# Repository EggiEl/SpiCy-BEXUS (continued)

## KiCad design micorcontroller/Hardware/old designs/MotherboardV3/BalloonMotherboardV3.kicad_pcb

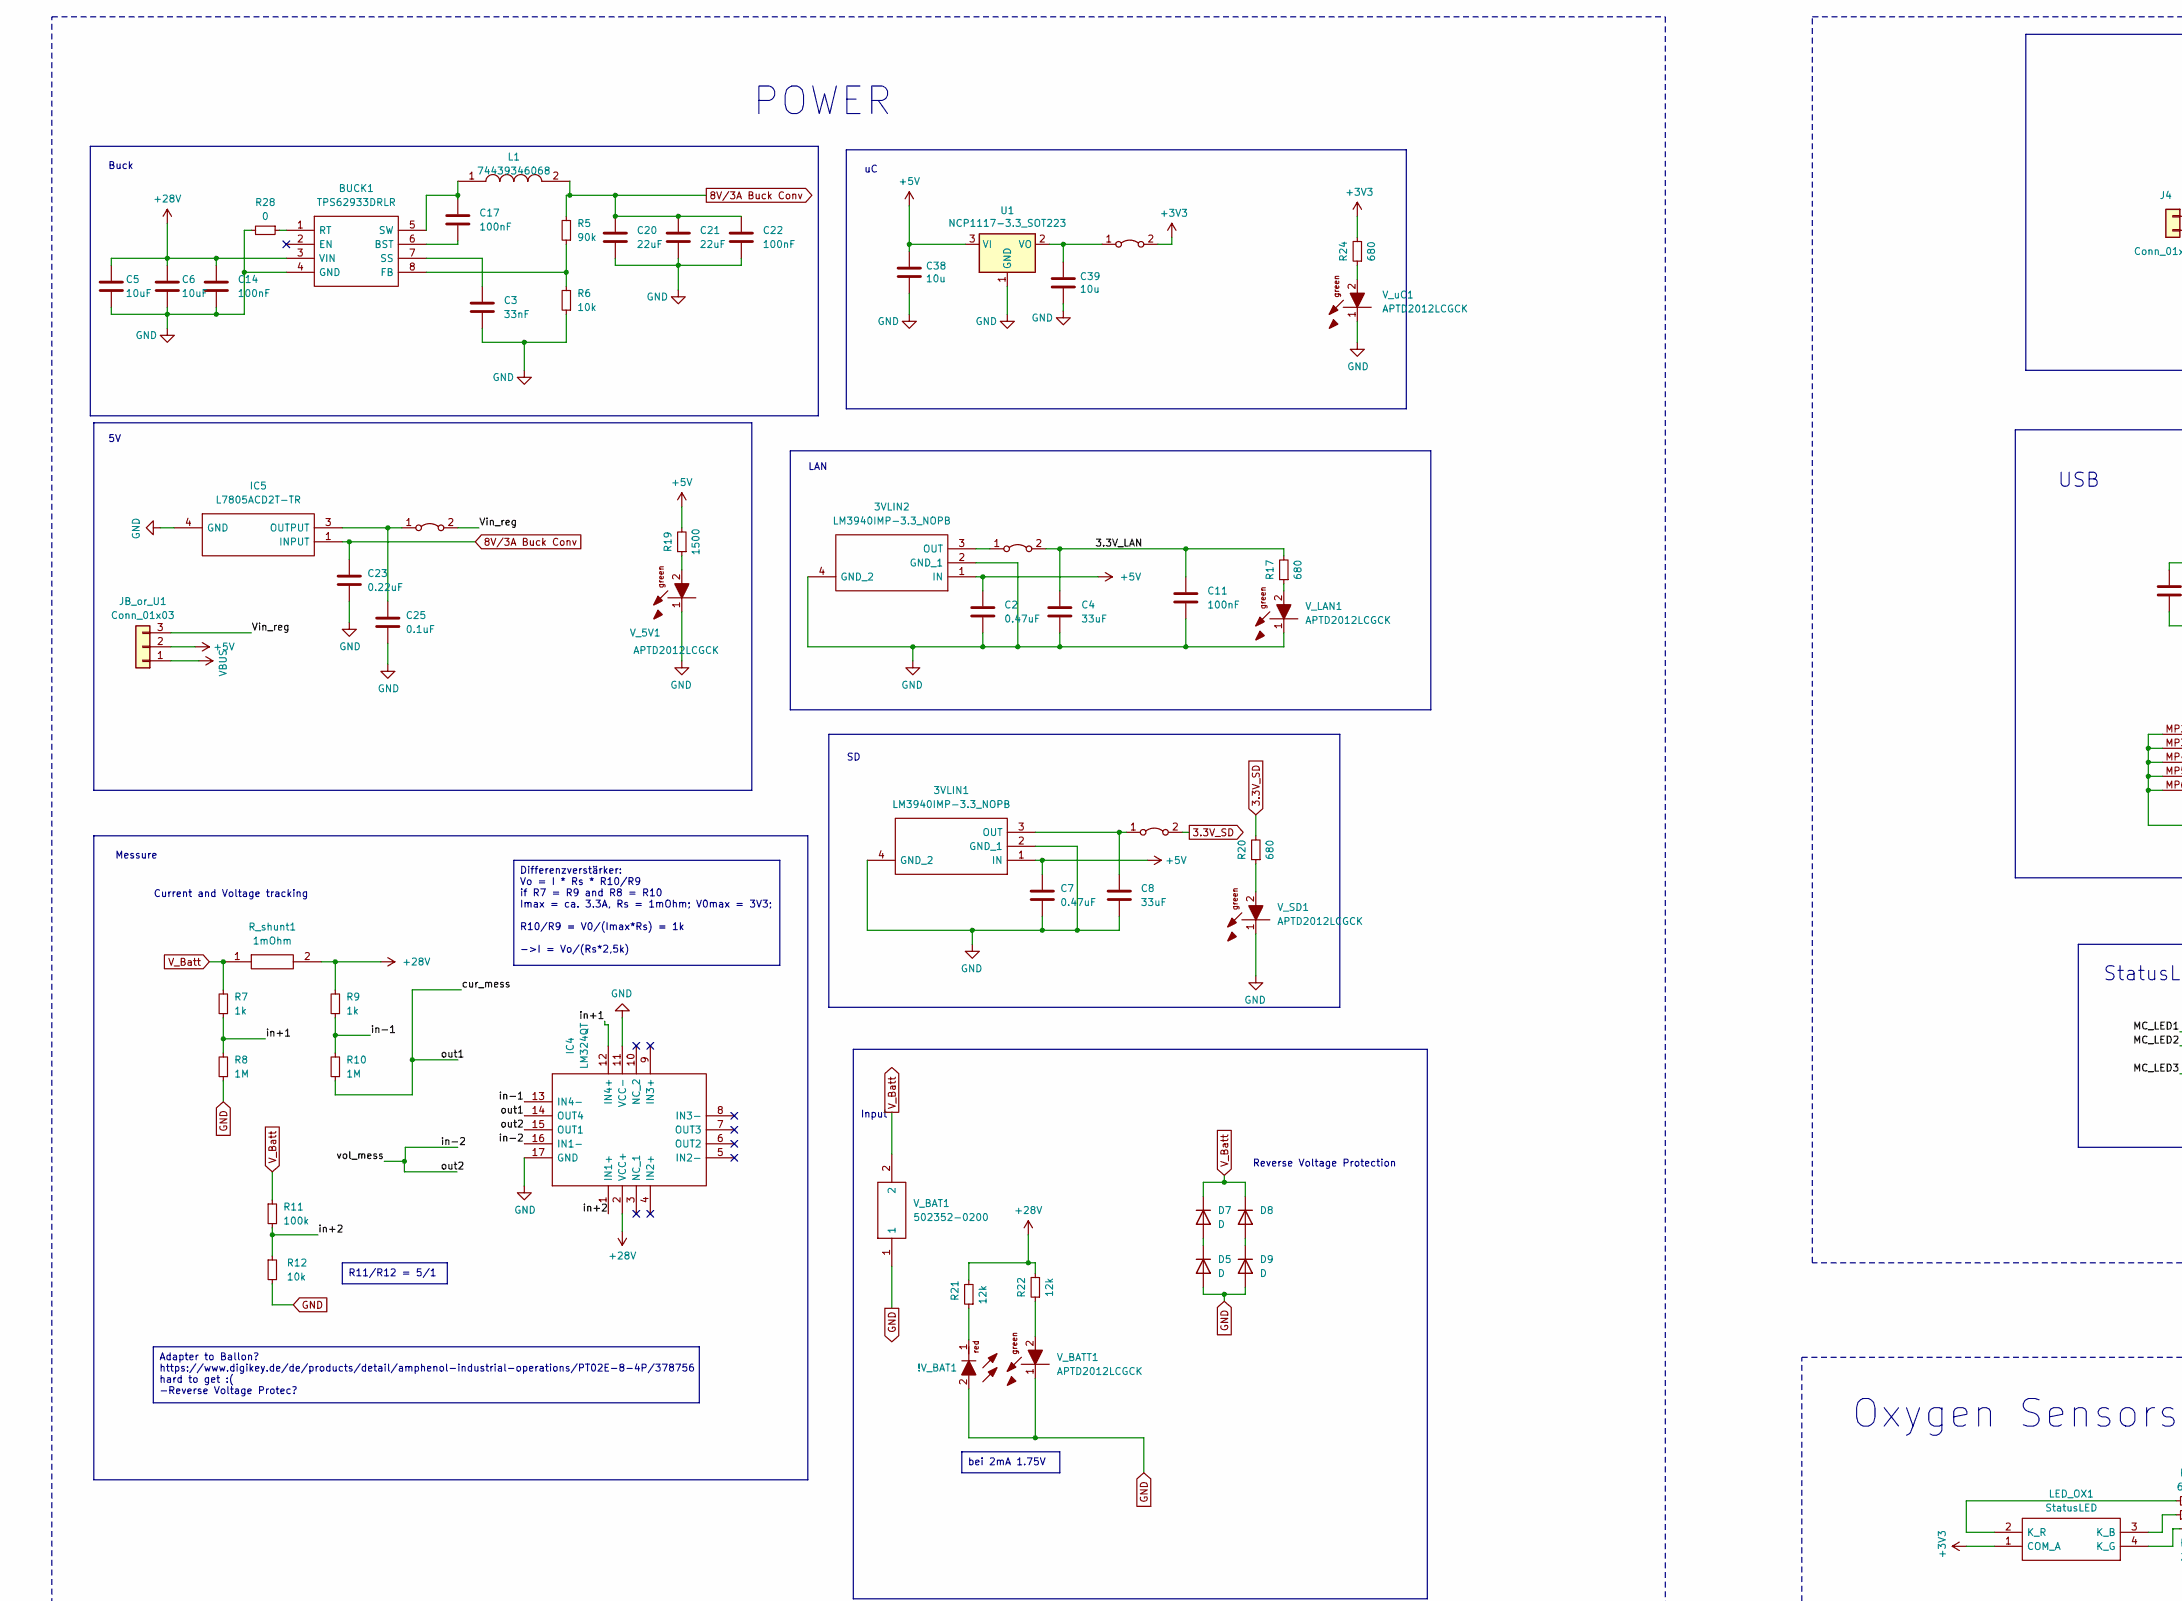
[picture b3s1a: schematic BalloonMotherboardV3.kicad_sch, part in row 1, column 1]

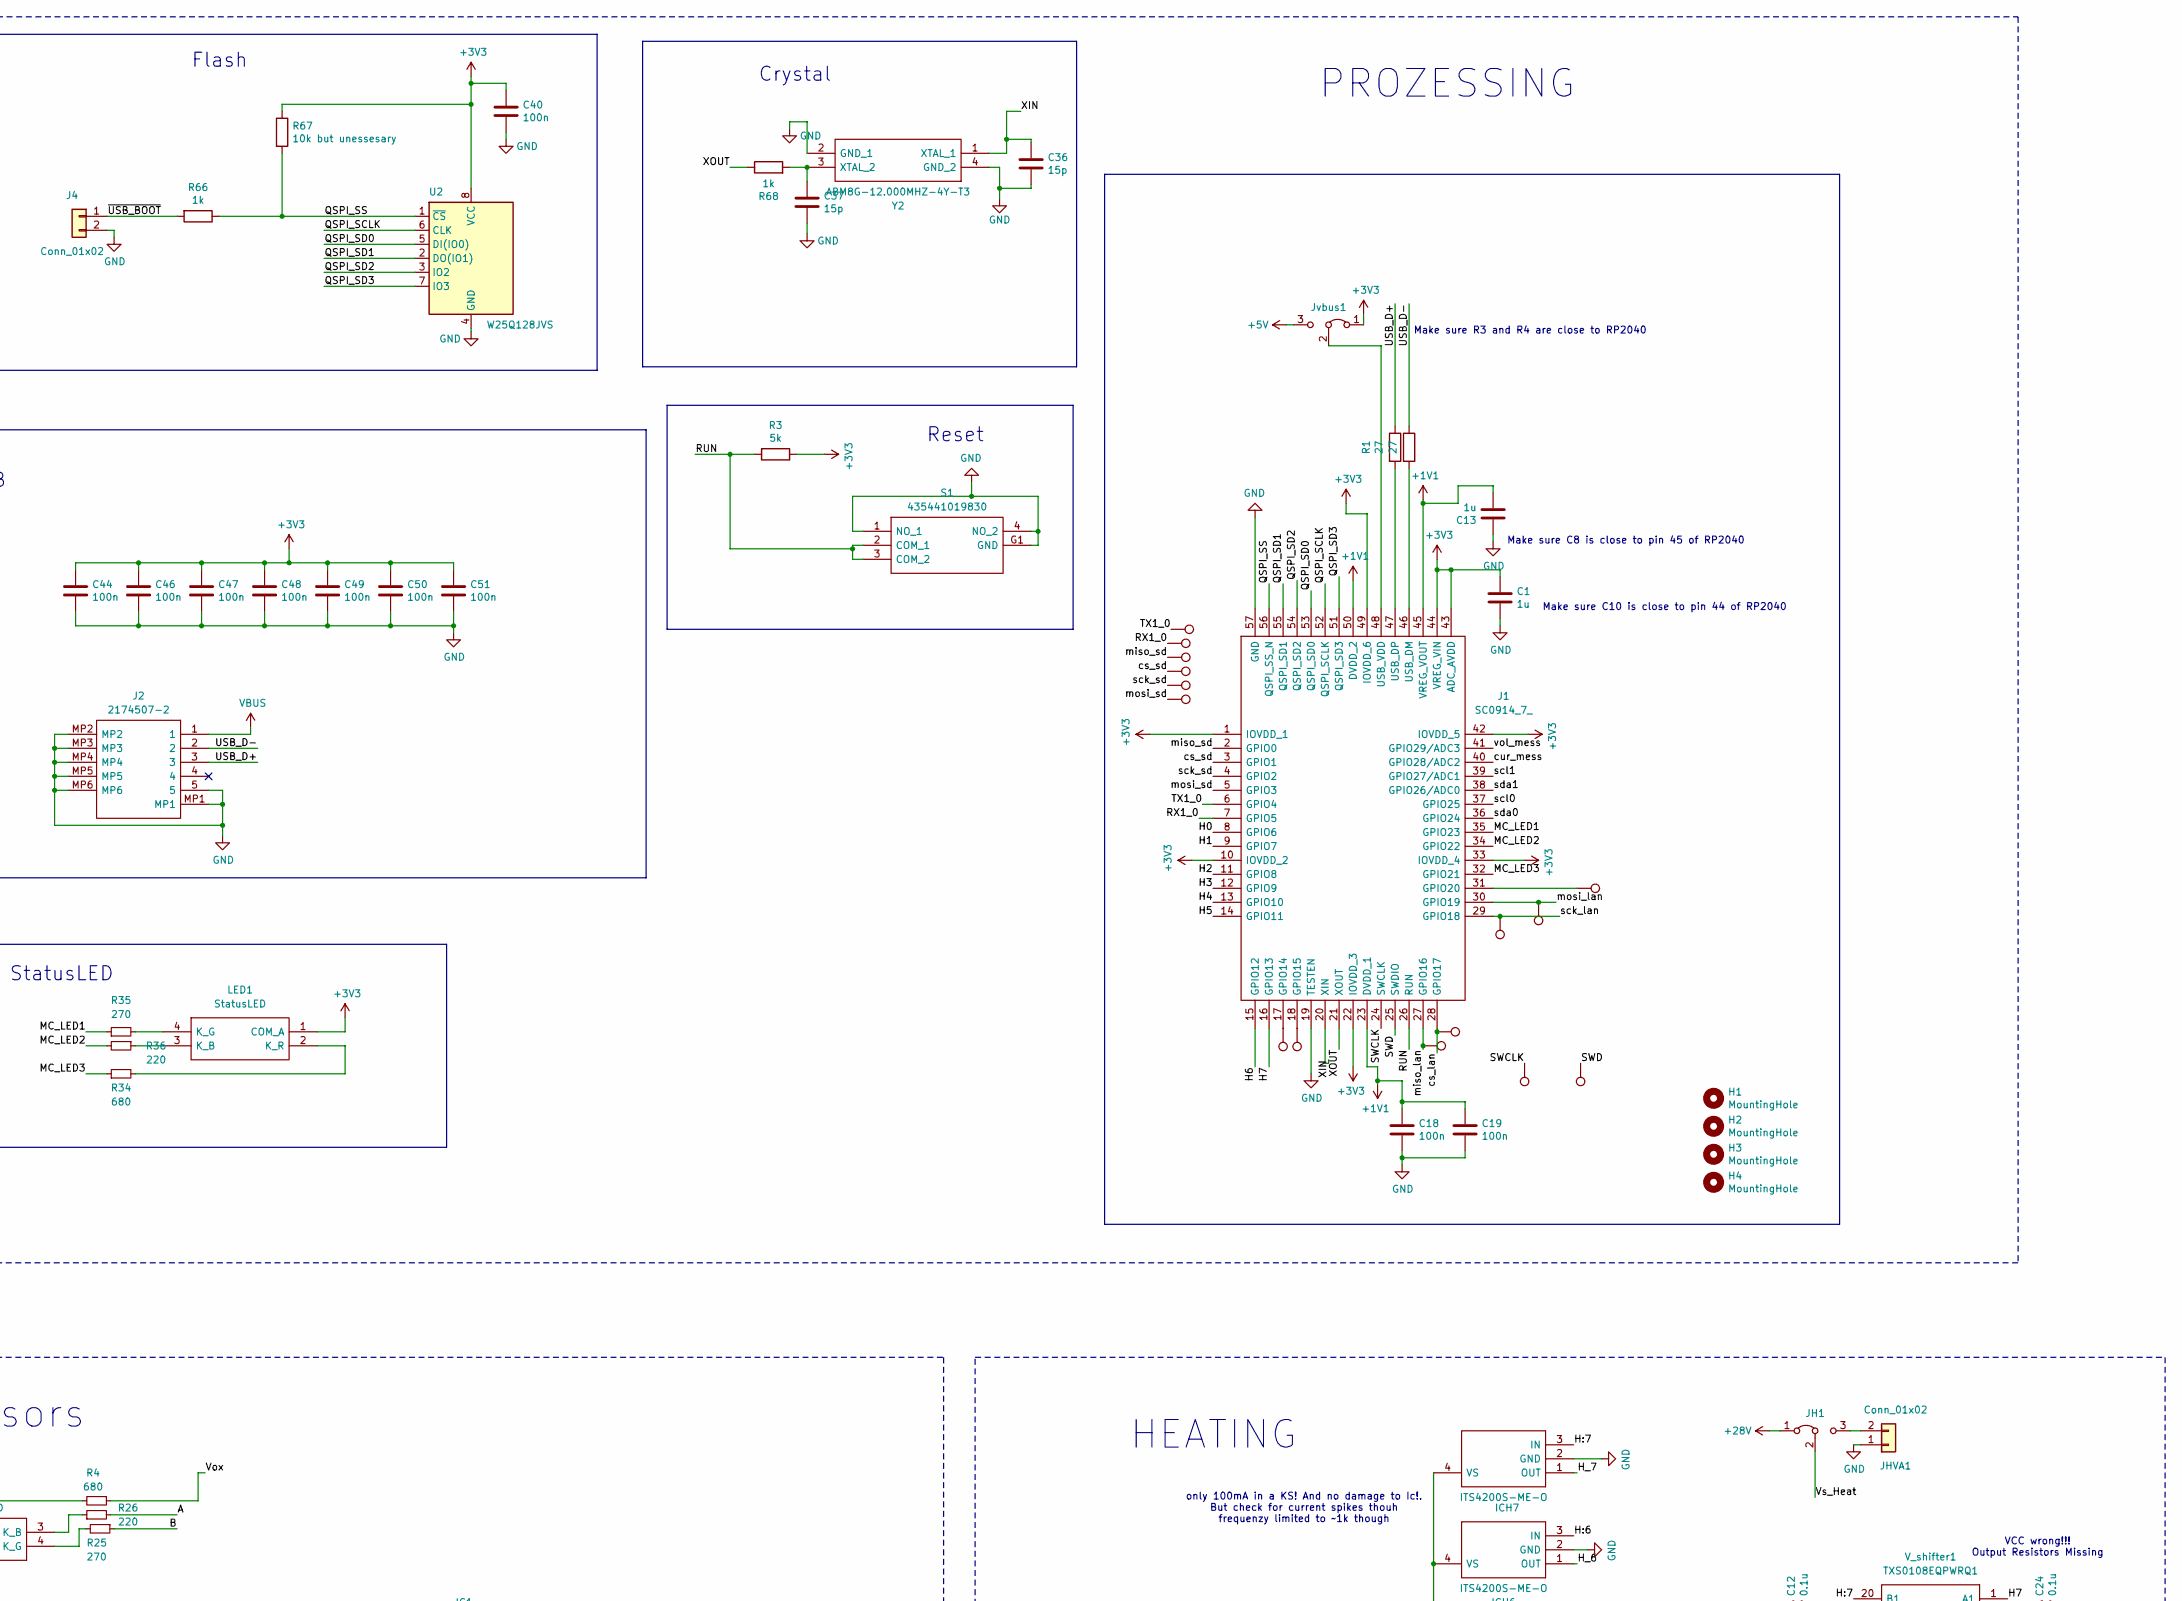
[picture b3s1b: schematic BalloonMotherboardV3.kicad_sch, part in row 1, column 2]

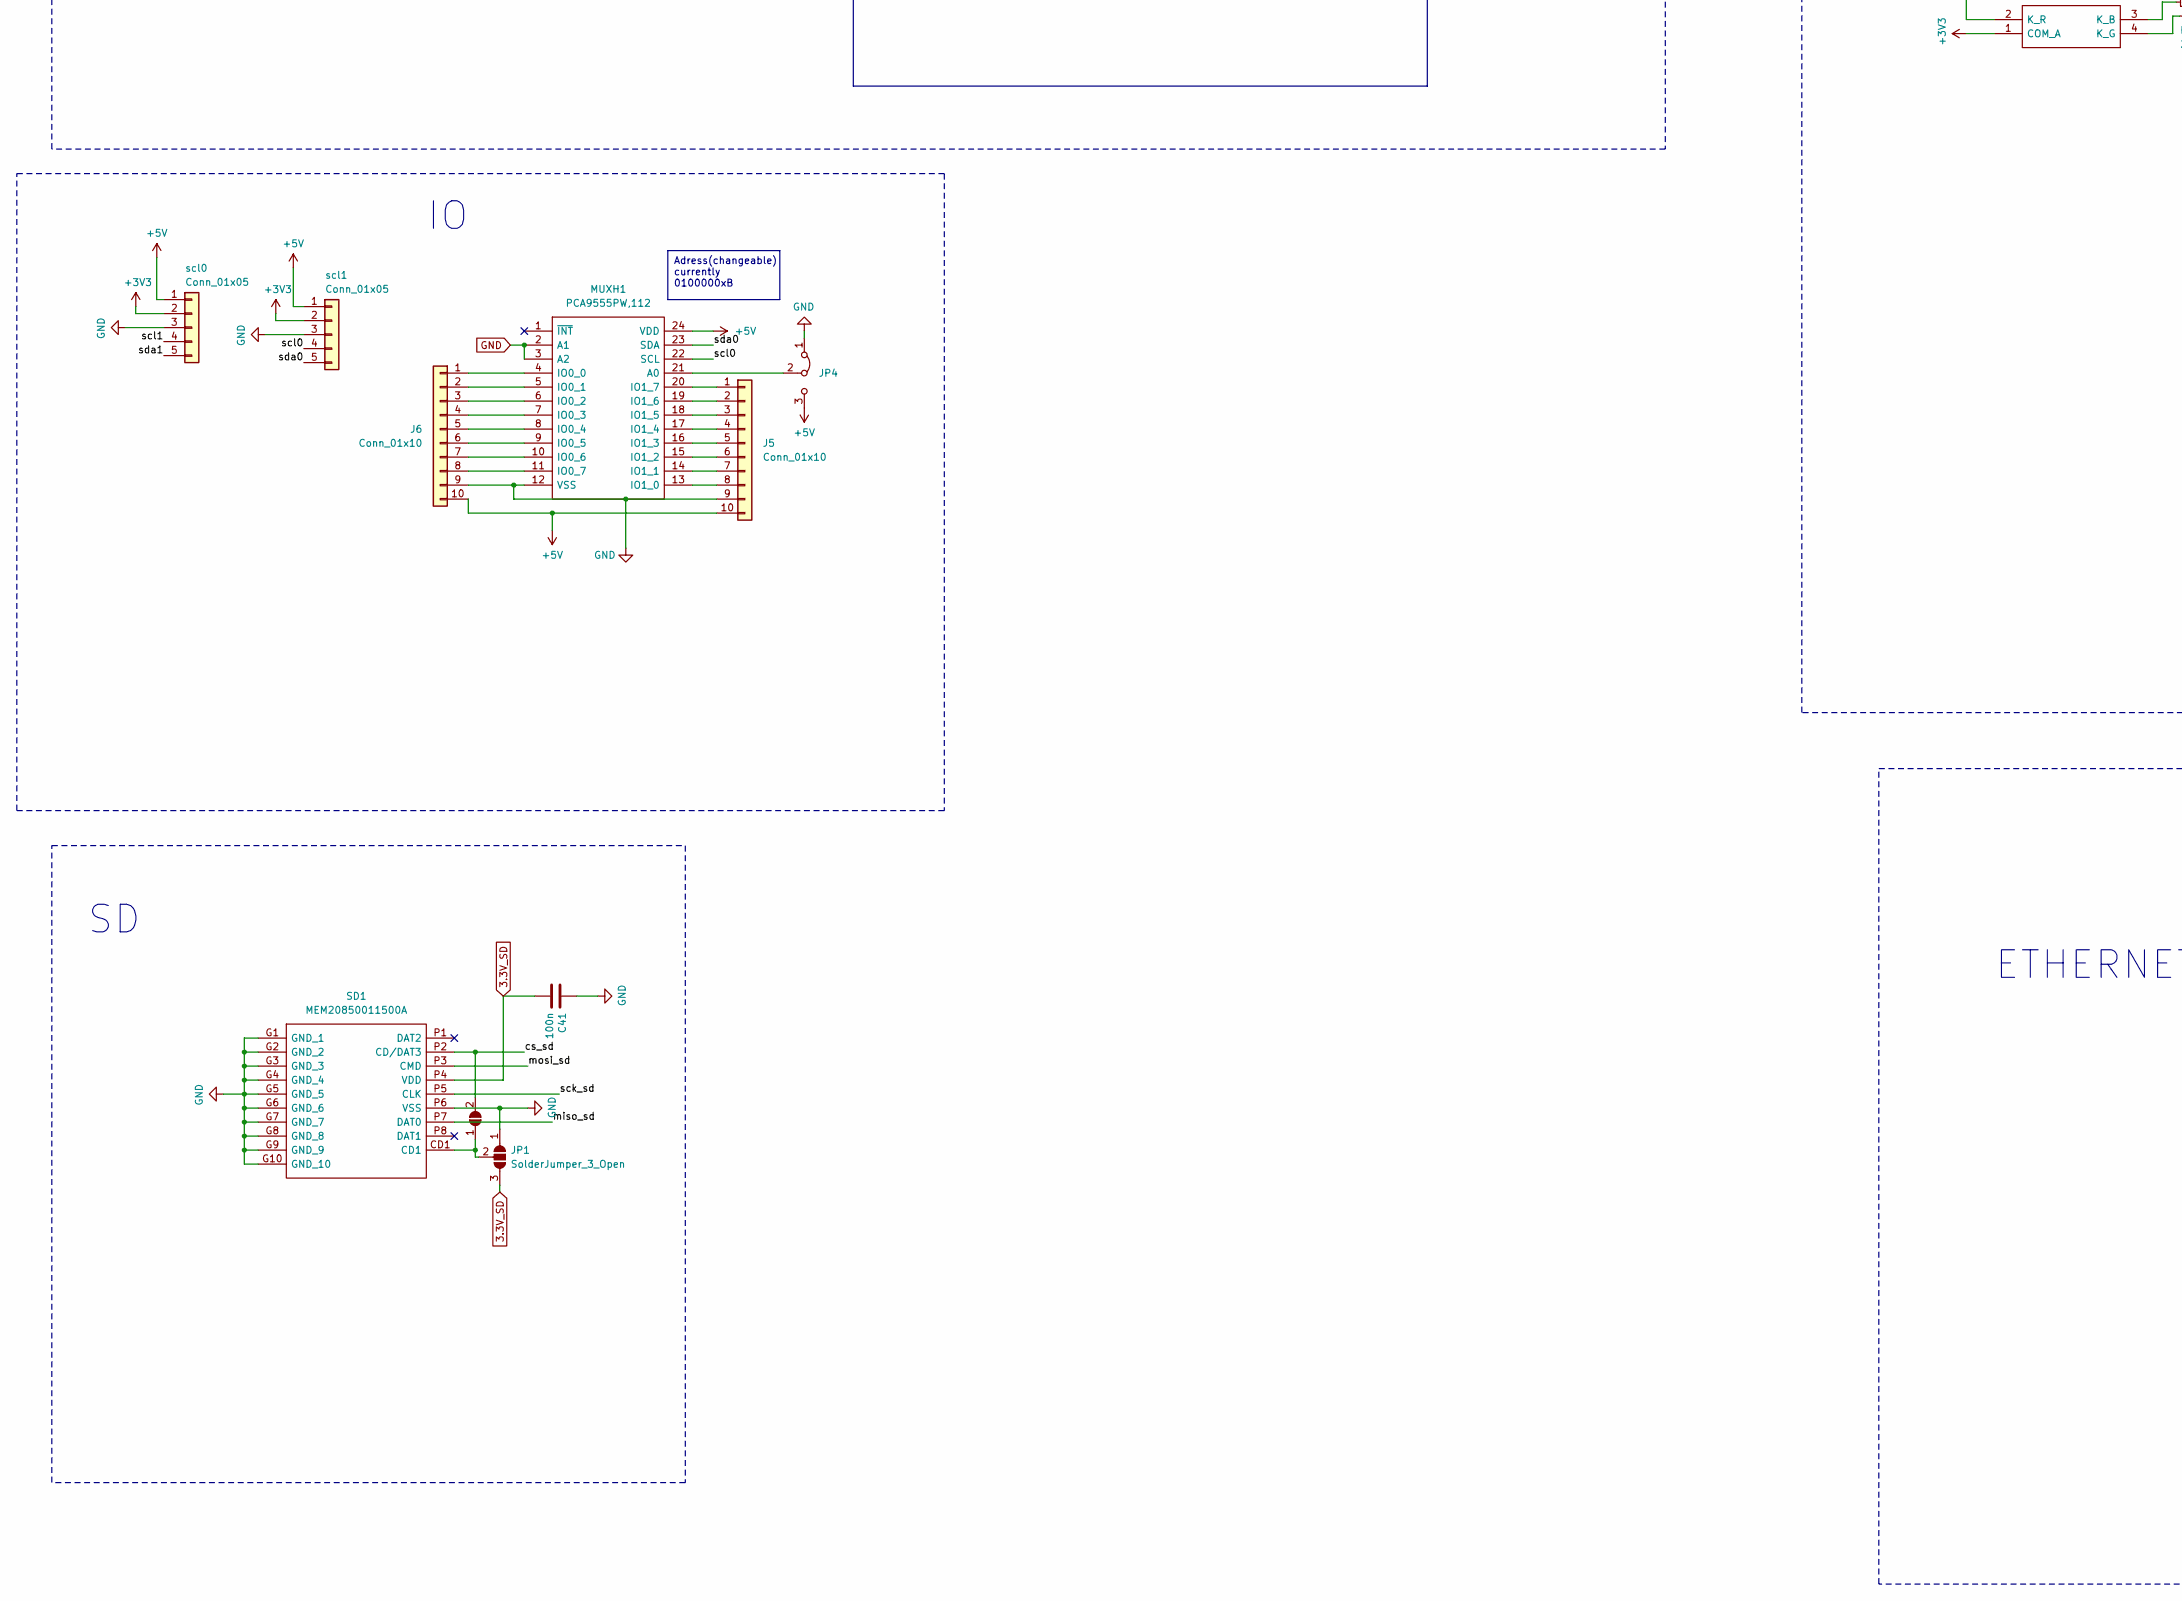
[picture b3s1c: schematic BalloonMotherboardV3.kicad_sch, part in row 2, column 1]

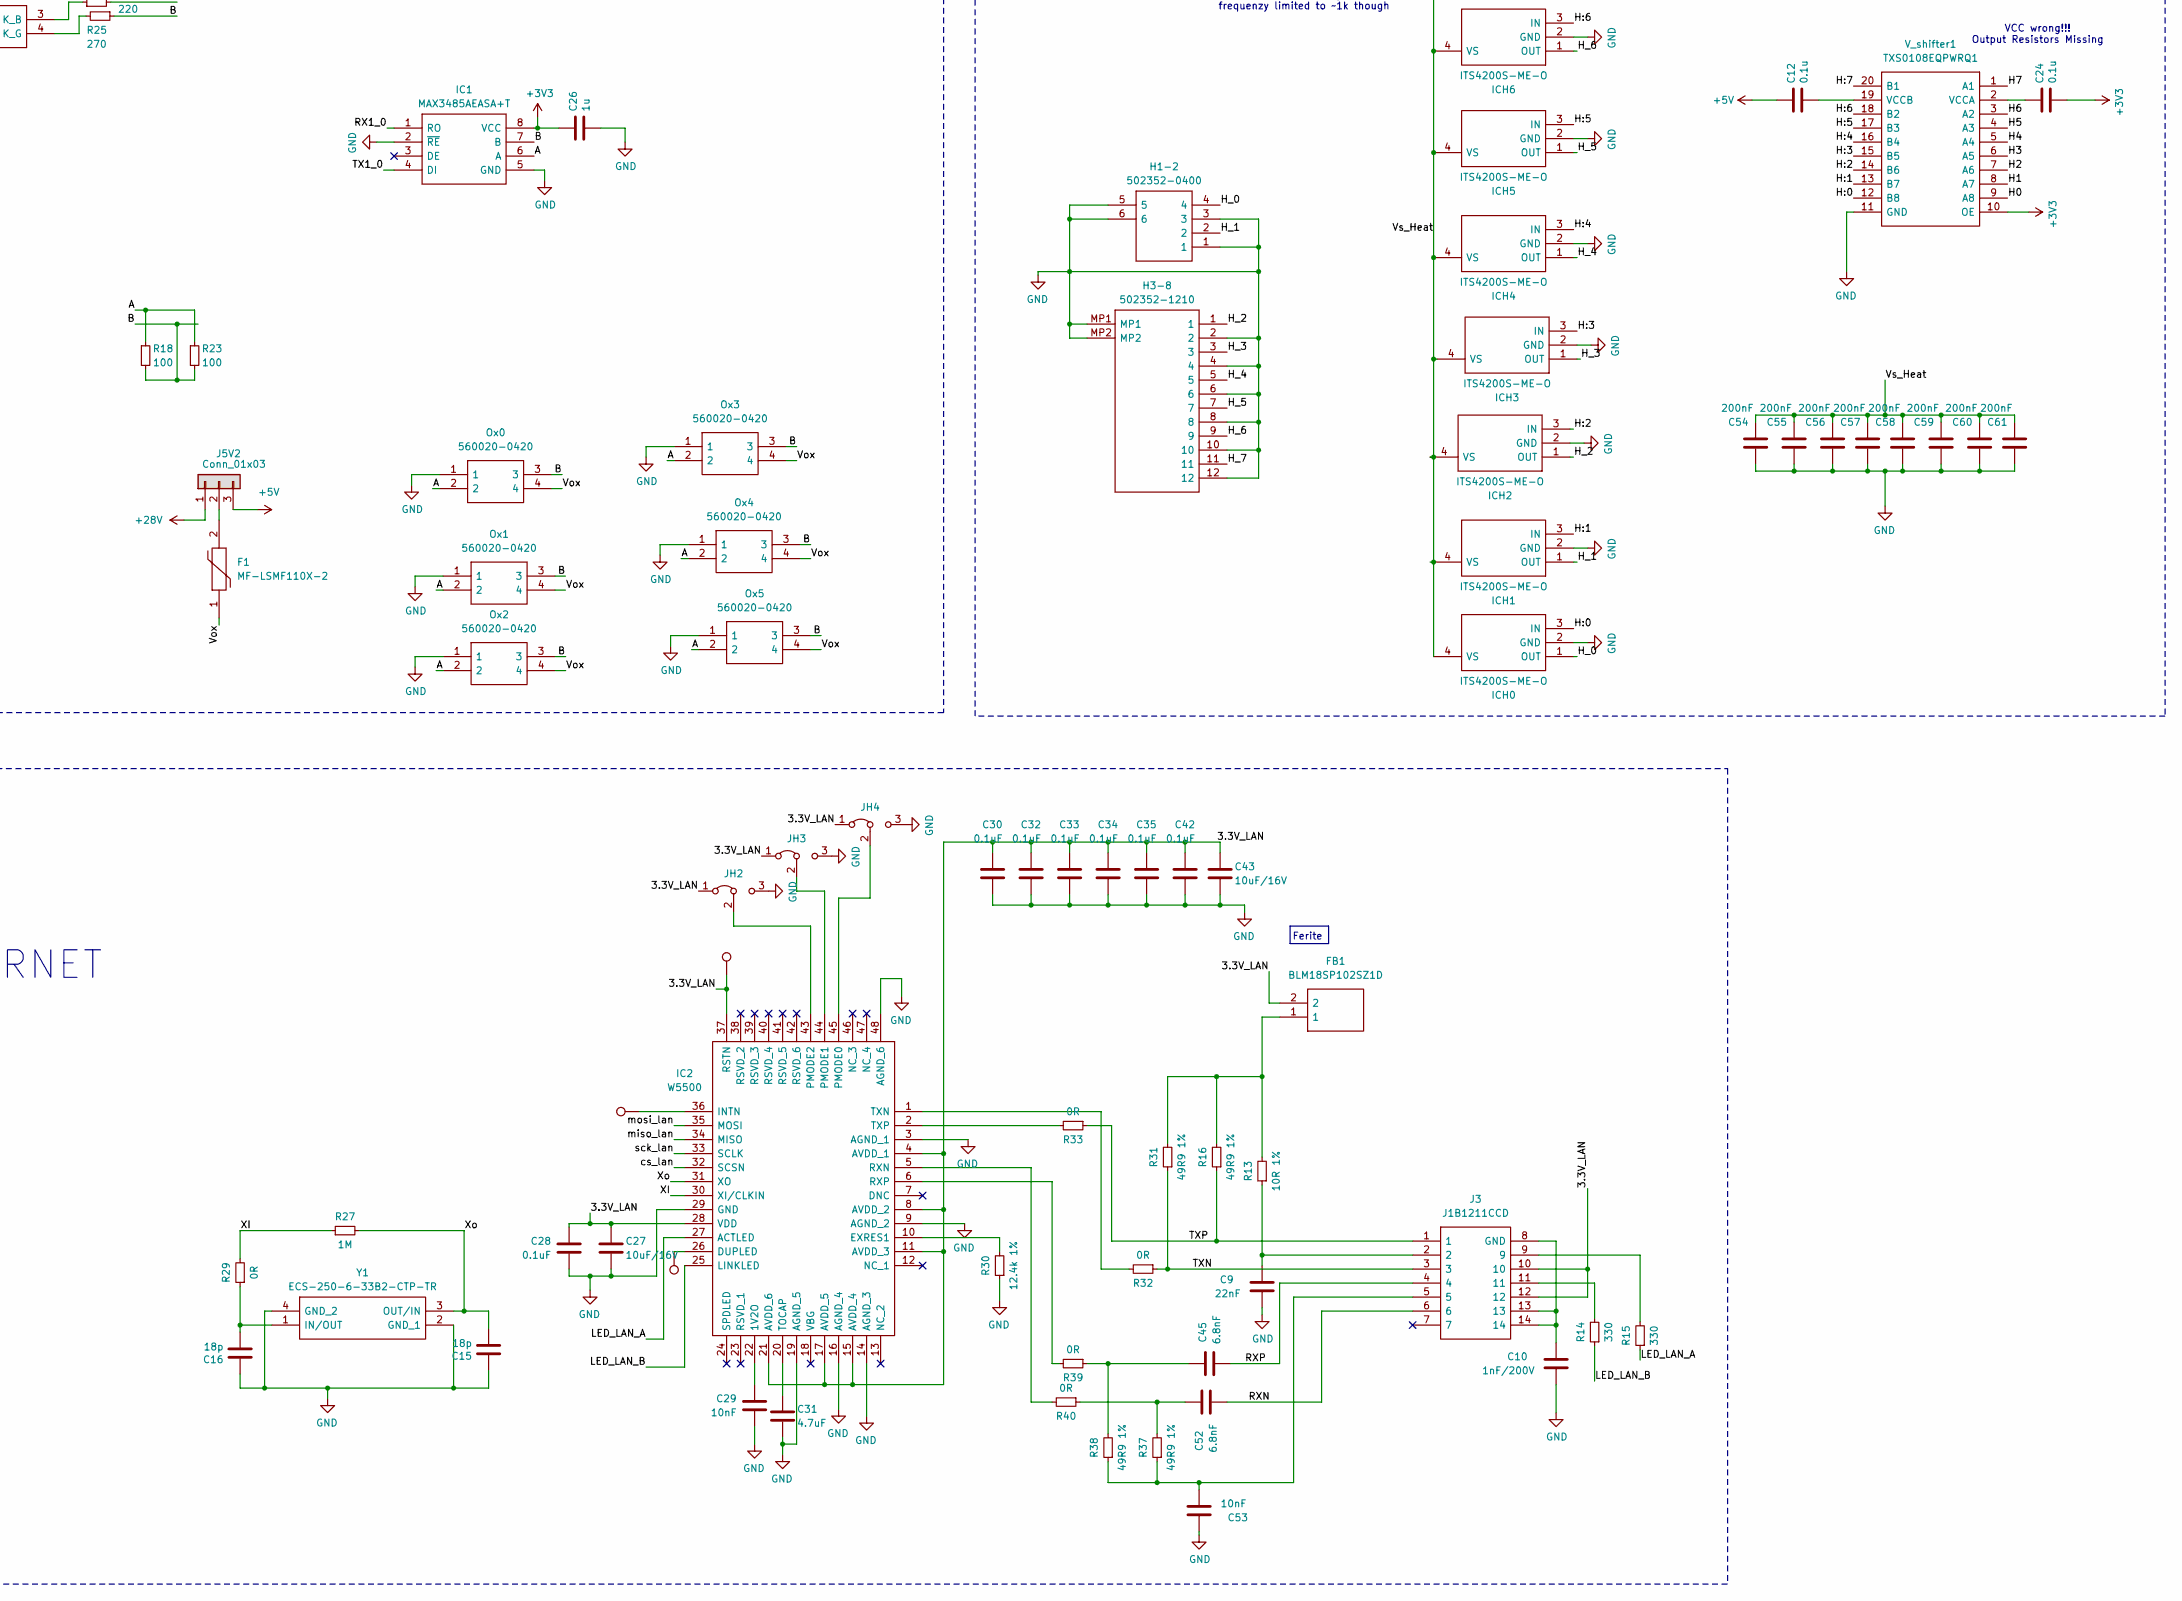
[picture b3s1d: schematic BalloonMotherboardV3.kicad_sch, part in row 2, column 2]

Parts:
3VLIN1, 3VLIN2: LM3940IMP-3.3_NOPB; SOT230P700X180-4N; Mouser Part Number 926-LM3940IMP3.3NOPB
!V_BAT1: APTD2012LSURCK; LEDM2012X120N; Mouser Part Number 604-APTD2012LSURCK
BUCK1: TPS62933DRLR; SOTFL50P160X60-8N; Mouser Part Number 595-TPS62933DRLR
C1, C13: 1u; C_0402_1005Metric
C2, C7: 0.47uF; C_0603_1608Metric
C3: 33nF; C_0603_1608Metric
C4, C8: 33uF; C_0603_1608Metric
C5, C6: 10uF; C_1206_3216Metric_Pad1.33x1.80mm_HandSolder
C9: 22nF; C_0402_1005Metric
C10: 1nF/200V; C_0402_1005Metric
C11, C14, C17, C22: 100nF; C_0603_1608Metric
C12, C24: 0.1u; C_0402_1005Metric
C15, C16: 18p; C_0402_1005Metric
C18, C19, C40, C41, C44, C46, C47, C48, C49, C50, C51: 100n; C_0402_1005Metric
C20, C21: 22uF; C_0603_1608Metric
C23: 0.22uF; C_0603_1608Metric
C25: 0.1uF; C_0603_1608Metric
C26: 1u; C_0805_2012Metric
C27, C43: 10uF/16V; C_1206_3216Metric_Pad1.33x1.80mm_HandSolder
C28, C30, C32, C33, C34, C35, C42: 0.1uF; C_0402_1005Metric
C29, C53: 10nF; C_0402_1005Metric
C31: 4.7uF; C_1206_3216Metric_Pad1.33x1.80mm_HandSolder
C36, C37: 15p; C_0402_1005Metric
C38, C39: 10u; C_0805_2012Metric
C45, C52: 6.8nF; C_0402_1005Metric
C54, C55, C56, C57, C58, C59, C60, C61: 200nF; C_0402_1005Metric
D5, D7, D9: D; DIOM5336X245N
D8: RBR2LB60BTBR1; DIOM5336X245N
F1: MF-LSMF110X-2; MFLSMF110X2; Mouser Part Number 652-MF-LSMF110X-2
FB1: BLM18SP102SZ1D; BLM18SP221SN1B; Mouser Part Number 81-BLM18SP102SZ1D
H1, H2, H3, H4: MountingHole; MountingHole_3.2mm_M3_DIN965_Pad_TopBottom
H1-2: 502352-0400; 5023520400; Mouser Part Number 538-502352-0400
H3-8: 502352-1210; 5023521210; Mouser Part Number 538-502352-1210
IC1: MAX3485AEASA+T; SOIC127P600X175-8N; Mouser Part Number 700-MAX3485AEASA+T
IC2: W5500; QFP50P900X900X160-48N; Mouser Part Number 950-W5500
IC4: LM324QT; QFN50P300X300X100-17N; Mouser Part Number 511-LM324QT
IC5: L7805ACD2T-TR; D2PAK-STB35NF10T4; Mouser Part Number 511-L7805ACD2T-TR
ICH0, ICH1, ICH2, ICH3, ICH4, ICH5, ICH6, ICH7: ITS4200S-ME-O; SOT230P700X170-4N; Mouser Part Number 726-ITS4200S-ME-O
J1: SC0914_7_; QFN40P700X700X90-57N-D; Mouser Part Number 358-SC09147
J2: 2174507-2; 21745072; Mouser Part Number 571-2174507-2
J3: J1B1211CCD; Mouser Part Number 950-J1B1211CCD
J4: Conn_01x02; PinHeader_1x02_P2.54mm_Vertical
J5, J6: Conn_01x10; PinHeader_1x10_P2.54mm_Vertical
J5V2: Conn_01x03; PinHeader_1x03_P2.54mm_Vertical
JB_or_U1: Conn_01x03; PinHeader_1x03_P2.54mm_Vertical
JH1, JH2, JH3, JH4: Jumper_3_Bridged12; SolderJumper-3_P1.3mm_Bridged12_RoundedPad1.0x1.5mm_NumberL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
JHVA1: Conn_01x02; PinHeader_1x02_P2.54mm_Vertical
JP1: SolderJumper_3_Open; SolderJumper-3_P1.3mm_Open_RoundedPad1.0x1.5mm_NumberLabels
JP3, JP5, JP9, JP10: Jumper_2_Bridged; SolderJumper-2_P1.3mm_Bridged2Bar_RoundedPad1.0x1.5mm
JP4: Jumper_3_Bridged12; SolderJumper-3_P1.3mm_Bridged12_RoundedPad1.0x1.5mm_NumberL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
JP11: SolderJumper_2_Open; SolderJumper-2_P1.3mm_Open_Pad1.0x1.5mm
Jvbus1: Jumper_3_Bridged12; SolderJumper-3_P1.3mm_Bridged12_RoundedPad1.0x1.5mm_NumberL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
L1: 74439346068; Mouser Part Number 710-74439346068
LED1: StatusLED; LTRBR37G4R4S01250; Mouser Part Number 720-LTRBR37GA6714
LED_OX1: StatusLED; LTRBR37G4R4S01250; Mouser Part Number 720-LTRBR37GA6714
MUXH1: PCA9555PW,112; SOP65P640X110-24N; Mouser Part Number 771-PCA9555PW
Ox0, Ox1, Ox2, Ox3, Ox4, Ox5: 560020-0420; Mouser Part Number 538-560020-0420
R1, R2: 27; R_0402_1005Metric
R3: 5k; R_0402_1005Metric
R4, R17, R20, R24, R34: 680; R_0805_2012Metric_Pad1.20x1.40mm_HandSolder
R5: 90k; R_0603_1608Metric
R6: 10k; R_0603_1608Metric
R7, R9: 1k; R_0805_2012Metric_Pad1.20x1.40mm_HandSolder
R8, R10: 1M; R_0805_2012Metric_Pad1.20x1.40mm_HandSolder
R11: 100k; R_0805_2012Metric_Pad1.20x1.40mm_HandSolder
R12: 10k; R_0402_1005Metric
R13: 10R 1%; R_0402_1005Metric
R14, R15: 330; R_0402_1005Metric
R16, R31, R37, R38: 49R9 1%; R_0402_1005Metric
R18, R23: 100; R_0805_2012Metric_Pad1.20x1.40mm_HandSolder
R19: 1500; R_0805_2012Metric_Pad1.20x1.40mm_HandSolder
R21, R22: 12k; R_0805_2012Metric_Pad1.20x1.40mm_HandSolder
R25, R35: 270; R_0805_2012Metric_Pad1.20x1.40mm_HandSolder
R26, R36: 220; R_0805_2012Metric_Pad1.20x1.40mm_HandSolder
R27: 1M; R_0402_1005Metric
R28: 0; R_0603_1608Metric
R29, R32, R33, R39, R40: 0R; R_0402_1005Metric
R30: 12.4k 1%; R_0402_1005Metric
R66, R68: 1k; R_0402_1005Metric
R67: 10k but unessesary; R_0402_1005Metric
R_shunt1: 1mOhm; RESC3216X90N; Mouser Part Number 603-PA1206FRE7W0R01Z
S1: 435441019830; Mouser Part Number 710-435441019830
SD1: MEM20850011500A; Mouser Part Number 640-MEM20850011500A
TP1, TP2, TP3, TP4, TP5, TP6, TP7, TP8, TP9, TP10, TP11, TP12, TP13, TP14, TP15, TP16, TP17, TP18: TestPoint; TestPoint_Pad_D1.0mm
U1: NCP1117-3.3_SOT223; SOT-223-3_TabPin2
U2: W25Q128JVS; SOIC-8_5.23x5.23mm_P1.27mm
V_5V1: APTD2012LCGCK; LEDC2012X120N; Mouser Part Number 604-APTD2012LCGCK
V_BAT1: 502352-0200; 5023520200; Mouser Part Number 538-502352-0200
V_BATT1: APTD2012LCGCK; LEDC2012X120N; Mouser Part Number 604-APTD2012LCGCK
V_LAN1: APTD2012LCGCK; LEDC2012X120N; Mouser Part Number 604-APTD2012LCGCK
V_SD1: APTD2012LCGCK; LEDC2012X120N; Mouser Part Number 604-APTD2012LCGCK
V_shifter1: TXS0108EQPWRQ1; SOP65P640X120-20N; Mouser Part Number 595-TXS0108EQPWRQ1
V_uC1: APTD2012LCGCK; LEDC2012X120N; Mouser Part Number 604-APTD2012LCGCK
Y1: ECS-250-6-33B2-CTP-TR; ECS250633B2CTPTR; Mouser Part Number 520-250-6-33B2-CTPTR
Y2: ABM8G-12.000MHZ-4Y-T3; ABM8G; Mouser Part Number 815-ABM8G-12-4YT3
scl0, scl1: Conn_01x05; PinHeader_1x05_P2.54mm_Vertical

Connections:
3.3V_SD: C41.2, JP1.3 (B), JP9.2 (B), R20.2, SD1.P4 (VDD)
8V/3A Buck Conv: C20.2, C21.2, C22.2, C23.2, IC5.1 (INPUT), L1.2, R5.2
+1V1: C13.2, C18.1, C19.1, J1.23 (DVDD_1), J1.45 (VREG_VOUT), J1.50 (DVDD_2)
+3V3: C1.1, C24.2, C26.1, C40.1, C44.1, C46.1, C47.1, C48.1, C49.1, C50.1, C51.1, IC1.8 (VCC), J1.1 (IOVDD_1), J1.10 (IOVDD_2), J1.22 (IOVDD_3), J1.33 (IOVDD_4), J1.42 (IOVDD_5), J1.43 (ADC_AVDD), J1.44 (VREG_VIN), J1.49 (IOVDD_6), JP10.2 (B), Jvbus1.1 (A), LED1.1 (COM_A), LED_OX1.1 (COM_A), R3.1, R24.2, R67.1, U2.8 (VCC), V_shifter1.10 (OE), scl0.2, scl1.2
+5V: 3VLIN1.1 (IN), 3VLIN2.1 (IN), C2.2, C7.2, C12.1, C38.1, J5.10, J5V2.3, J6.10, JB_or_U1.2, JP4.3 (B), Jvbus1.3 (B), MUXH1.24 (VDD), R19.2, U1.3 (VI), scl0.1, scl1.1
+28V: BUCK1.3 (VIN), C5.2, C6.2, C14.2, IC4.2 (VCC+), J5V2.1, JH1.1 (A), R9.2, R21.2, R22.2, R_shunt1.2
/3.3V_LAN: C4.2, C11.2, C27.2, C28.2, C30.2, C32.2, C33.2, C34.2, C35.2, C42.2, C43.2, FB1.2, IC2.4 (AVDD_1), IC2.8 (AVDD_2), IC2.11 (AVDD_3), IC2.15 (AVDD_4), IC2.17 (AVDD_5), IC2.21 (AVDD_6), IC2.28 (VDD), IC2.37 (RSTN), J3.10, J3.12, JH2.1 (A), JH3.1 (A), JH4.1 (A), JP3.2 (B), R17.2, TP17.1
/A: IC1.6 (A), Ox0.2, Ox1.2, Ox2.2, Ox3.2, Ox4.2, Ox5.2, R18.1, R23.1, R26.2
/B: IC1.7 (B), Ox0.3, Ox1.3, Ox2.3, Ox3.3, Ox4.3, Ox5.3, R18.2, R23.2, R25.1
/H0: J1.8 (GPIO6), V_shifter1.9 (A8)
/H1: J1.9 (GPIO7), V_shifter1.8 (A7)
/H2: J1.11 (GPIO8), V_shifter1.7 (A6)
/H3: J1.12 (GPIO9), V_shifter1.6 (A5)
/H4: J1.13 (GPIO10), V_shifter1.5 (A4)
/H5: J1.14 (GPIO11), V_shifter1.4 (A3)
/H6: J1.15 (GPIO12), V_shifter1.3 (A2)
/H7: J1.16 (GPIO13), V_shifter1.1 (A1)
/H:0: ICH0.3 (IN), V_shifter1.12 (B8)
/H:1: ICH1.3 (IN), V_shifter1.13 (B7)
/H:2: ICH2.3 (IN), V_shifter1.14 (B6)
/H:3: ICH3.3 (IN), V_shifter1.15 (B5)
/H:4: ICH4.3 (IN), V_shifter1.16 (B4)
/H:5: ICH5.3 (IN), V_shifter1.17 (B3)
/H:6: ICH6.3 (IN), V_shifter1.18 (B2)
/H:7: ICH7.3 (IN), V_shifter1.20 (B1)
/H_0: H1-2.4, ICH0.1 (OUT)
/H_1: H1-2.2, ICH1.1 (OUT)
/H_2: H3-8.1, ICH2.1 (OUT)
/H_3: H3-8.3, ICH3.1 (OUT)
/H_4: H3-8.5, ICH4.1 (OUT)
/H_5: H3-8.7, ICH5.1 (OUT)
/H_6: H3-8.9, ICH6.1 (OUT)
/H_7: H3-8.11, ICH7.1 (OUT)
/LED_LAN_A: IC2.27 (ACTLED), R15.1
/LED_LAN_B: IC2.25 (LINKLED), R14.1
/MC_LED1: J1.35 (GPIO23), R35.1
/MC_LED2: J1.34 (GPIO22), R36.2
/MC_LED3: J1.32 (GPIO21), R34.1
/QSPI_SCLK: J1.52 (QSPI_SCLK), U2.6 (CLK)
/QSPI_SD0: J1.53 (QSPI_SD0), U2.5 (DI(IO0))
/QSPI_SD1: J1.55 (QSPI_SD1), U2.2 (DO(IO1))
/QSPI_SD2: J1.54 (QSPI_SD2), U2.3 (IO2)
/QSPI_SD3: J1.51 (QSPI_SD3), U2.7 (IO3)
/QSPI_SS: J1.56 (QSPI_SS_N), R66.1, R67.2, U2.1 (~CS)
/RUN: J1.26 (RUN), R3.2, S1.2 (COM_1), S1.3 (COM_2)
/RX1_0: IC1.1 (RO), J1.7 (GPIO5), TP11.1
/RXN: C52.1, J3.6
/RXP: C45.1, J3.4
/SWCLK: J1.24 (SWCLK), TP12.1
/SWD: J1.25 (SWDIO), TP1.1
/TX1_0: IC1.4 (DI), J1.6 (GPIO4), TP10.1
/TXN: J3.3, R31.1, R32.1
/TXP: J3.1, R16.1, R33.1
/USB_D+: J2.3, R1.1
/USB_D-: J2.2, R2.1
/Vin_reg: JB_or_U1.3, JP5.2 (B)
/Vox: F1.1, Ox0.4, Ox1.4, Ox2.4, Ox3.4, Ox4.4, Ox5.4, R4.1
/Vs_Heat: C54.1, C55.1, C56.1, C57.1, C58.1, C59.1, C60.1, C61.1, ICH0.4 (VS), ICH1.4 (VS), ICH2.4 (VS), ICH3.4 (VS), ICH4.4 (VS), ICH5.4 (VS), ICH6.4 (VS), ICH7.4 (VS), JH1.2 (C)
/XI: IC2.30 (XI/CLKIN), R27.1, R29.2
/XIN: C36.1, J1.20 (XIN), Y2.1 (XTAL_1)
/XOUT: J1.21 (XOUT), R68.1
/Xo: C15.2, IC2.31 (XO), R27.2, Y1.3 (OUT/IN)
/cs_lan: IC2.32 (SCSN), J1.28 (GPIO17), TP4.1
/cs_sd: J1.3 (GPIO1), JP11.2 (B), SD1.P2 (CD/DAT3), TP6.1
/cur_mess: IC4.14 (OUT4), J1.40 (GPIO28/ADC2), R10.1
/in+1: IC4.12 (IN4+), R7.1, R8.2
/in+2: IC4.1 (IN1+), R11.2, R12.1
/in-1: IC4.13 (IN4-), R9.1, R10.2
/in-2: IC4.15 (OUT1), IC4.16 (IN1-), J1.41 (GPIO29/ADC3)
/miso_lan: IC2.34 (MISO), J1.27 (GPIO16), TP5.1
/miso_sd: J1.2 (GPIO0), SD1.P7 (DAT0), TP8.1
/mosi_lan: IC2.35 (MOSI), J1.30 (GPIO19), TP3.1
/mosi_sd: J1.5 (GPIO3), SD1.P3 (CMD), TP9.1
/sck_lan: IC2.33 (SCLK), J1.29 (GPIO18), TP2.1
/sck_sd: J1.4 (GPIO2), SD1.P5 (CLK), TP7.1
/scl0: J1.37 (GPIO25), MUXH1.22 (SCL), scl1.4
/scl1: J1.39 (GPIO27/ADC1), scl0.4
/sda0: J1.36 (GPIO24), MUXH1.23 (SDA), scl1.5
/sda1: J1.38 (GPIO26/ADC0), scl0.5
/~USB_BOOT: J4.1, R66.2
GND: 3VLIN1.2 (GND_1), 3VLIN1.4 (GND_2), 3VLIN2.2 (GND_1), 3VLIN2.4 (GND_2), !V_BAT1.2, BUCK1.4 (GND), C1.2, C2.1, C3.1, C4.1, C5.1, C6.1, C7.1, C8.1, C9.1, C10.1, C11.1, C13.1, C14.1, C15.1, C16.1, C18.2, C19.2, C20.1, C21.1, C22.1, C23.1, C25.1, C26.2, C27.1, C28.1, C29.1, C30.1, C31.1, C32.1, C33.1, C34.1, C35.1, C36.2, C37.2, C38.2, C39.2, C40.2, C41.1, C42.1, C43.1, C44.2, C46.2, C47.2, C48.2, C49.2, C50.2, C51.2, C53.2, C54.2, C55.2, C56.2, C57.2, C58.2, C59.2, C60.2, C61.2, D5.2 (A), D9.2 (A), H1-2.1, H1-2.3, H1-2.5, H1-2.6, H3-8.2, H3-8.4, H3-8.6, H3-8.8, H3-8.10, H3-8.12, H3-8.MP1, H3-8.MP2, IC1.2 (~RE), IC1.5 (GND), IC2.3 (AGND_1), IC2.9 (AGND_2), IC2.14 (AGND_3), IC2.16 (AGND_4), IC2.19 (AGND_5), IC2.29 (GND), IC2.48 (AGND_6), IC4.11 (VCC-), IC4.17 (GND), IC5.4 (GND), ICH0.2 (GND), ICH1.2 (GND), ICH2.2 (GND), ICH3.2 (GND), ICH4.2 (GND), ICH5.2 (GND), ICH6.2 (GND), ICH7.2 (GND), J1.19 (TESTEN), J1.57 (GND), J2.5, J2.MP1, J2.MP2, J2.MP3, J2.MP4, J2.MP5, J2.MP6, J4.2, J5.9, J6.9, JH2.3 (B), JH3.3 (B), JH4.3 (B), JHVA1.1, JP1.1 (A), JP4.1 (A), MUXH1.2 (A1), MUXH1.3 (A2), MUXH1.12 (VSS), Ox0.1, Ox1.1, Ox2.1, Ox3.1, Ox4.1, Ox5.1, R6.1, R8.1, R12.2, R28.2, R30.1, S1.1 (NO_1), S1.4 (NO_2), S1.G1 (GND), SD1.G1 (GND_1), SD1.G2 (GND_2), SD1.G3 (GND_3), SD1.G4 (GND_4), SD1.G5 (GND_5), SD1.G6 (GND_6), SD1.G7 (GND_7), SD1.G8 (GND_8), SD1.G9 (GND_9), SD1.G10 (GND_10), SD1.P6 (VSS), U1.1 (GND), U2.4 (GND), V_5V1.1, V_BAT1.1, V_BATT1.1, V_LAN1.1, V_SD1.1, V_shifter1.11 (GND), V_uC1.1, Y1.2 (GND_1), Y1.4 (GND_2), Y2.2 (GND_1), Y2.4 (GND_2), scl0.3, scl1.3
unnamed: 3VLIN1.3 (OUT), C8.2, JP9.1 (A)
unnamed: 3VLIN2.3 (OUT), JP3.1 (A)
unnamed: !V_BAT1.1, R21.1
unnamed: BUCK1.6 (BST), C17.1
unnamed: BUCK1.8 (FB), R5.1, R6.2
unnamed: BUCK1.1 (RT), R28.1
unnamed: BUCK1.7 (SS), C3.2
unnamed: BUCK1.5 (SW), C17.2, L1.1
unnamed: C9.2, J3.2, R13.1
unnamed: C45.2, R38.2, R39.1
unnamed: C52.2, R37.2, R40.1
unnamed: C53.1, J3.5, R37.1, R38.1
unnamed: D5.1 (K), D7.2 (A)
unnamed: D8.2 (A), D9.1 (K)
unnamed: FB1.1, R13.2, R16.2, R31.2
unnamed: C29.2, IC2.22 (1V2O)
unnamed: IC2.26 (DUPLED), TP15.1
unnamed: IC2.10 (EXRES1), R30.2
unnamed: IC2.36 (INTN), TP16.1
unnamed: IC2.45 (PMODE0), JH4.2 (C)
unnamed: IC2.44 (PMODE1), JH3.2 (C)
unnamed: IC2.43 (PMODE2), JH2.2 (C)
unnamed: IC2.5 (RXN), R40.2
unnamed: IC2.6 (RXP), R39.2
unnamed: C31.2, IC2.20 (TOCAP)
unnamed: IC2.1 (TXN), R32.2
unnamed: IC2.2 (TXP), R33.2
unnamed: C25.2, IC5.3 (OUTPUT), JP5.1 (A)
unnamed: J1.17 (GPIO14), TP13.1
unnamed: J1.18 (GPIO15), TP14.1
unnamed: J1.31 (GPIO20), TP18.1
unnamed: J1.46 (USB_DM), R2.2
unnamed: J1.47 (USB_DP), R1.2
unnamed: J1.48 (USB_VDD), Jvbus1.2 (C)
unnamed: C10.2, J3.8 (GND), J3.13, J3.14
unnamed: J3.9, R15.2
unnamed: J3.11, R14.2
unnamed: J5.1, MUXH1.20 (IO1_7)
unnamed: J5.2, MUXH1.19 (IO1_6)
unnamed: J5.3, MUXH1.18 (IO1_5)
unnamed: J5.4, MUXH1.17 (IO1_4)
unnamed: J5.5, MUXH1.16 (IO1_3)
unnamed: J5.6, MUXH1.15 (IO1_2)
unnamed: J5.7, MUXH1.14 (IO1_1)
unnamed: J5.8, MUXH1.13 (IO1_0)
unnamed: F1.2, J5V2.2
unnamed: J6.1, MUXH1.4 (IO0_0)
unnamed: J6.2, MUXH1.5 (IO0_1)
unnamed: J6.3, MUXH1.6 (IO0_2)
unnamed: J6.4, MUXH1.7 (IO0_3)
unnamed: J6.5, MUXH1.8 (IO0_4)
unnamed: J6.6, MUXH1.9 (IO0_5)
unnamed: J6.7, MUXH1.10 (IO0_6)
unnamed: J6.8, MUXH1.11 (IO0_7)
unnamed: JH1.3 (B), JHVA1.2
unnamed: JP1.2 (C), JP11.1 (A), SD1.CD1
unnamed: JP4.2 (C), MUXH1.21 (A0)
unnamed: C39.1, JP10.1 (A), U1.2 (VO)
unnamed: LED1.3 (K_B), R36.1
unnamed: LED1.4 (K_G), R35.2
unnamed: LED1.2 (K_R), R34.2
unnamed: LED_OX1.3 (K_B), R26.1
unnamed: LED_OX1.4 (K_G), R25.2
unnamed: LED_OX1.2 (K_R), R4.2
unnamed: R17.1, V_LAN1.2
unnamed: R19.1, V_5V1.2
unnamed: R20.1, V_SD1.2
unnamed: R22.1, V_BATT1.2
unnamed: R24.1, V_uC1.2
unnamed: C24.1, V_shifter1.2 (VCCA)
unnamed: C12.2, V_shifter1.19 (VCCB)
unnamed: C16.2, R29.1, Y1.1 (IN/OUT)
unnamed: C37.1, R68.2, Y2.3 (XTAL_2)
VBUS: J2.1, JB_or_U1.1
V_Batt: D7.1 (K), D8.1 (K), R7.2, R11.1, R_shunt1.1, V_BAT1.2

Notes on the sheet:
Adapter to Ballon? https://www.digikey.de/de/products/detail/amphenol-industrial-operations/PT02E-8-4P/378756 hard to get :( -Reverse Voltage Protec?
Ferite
R11/R12 = 5/1
Adress(changeable) currently 0100000xB
Differenzverstärker: Vo = I * Rs * R10/R9 if R7 = R9 and R8 = R10 Imax = ca. 3.3A, Rs = 1mOhm; V0max = 3V3; R10/R9 = V0/(Imax*Rs) = 1k ->I = Vo/(Rs*2,5k)
bei 2mA 1.75V
ETHERNET
PROZESSING
Make sure C8 is close to pin 45 of RP2040
Oxygen Sensors
Make sure R3 and R4 are close to RP2040
StatusLED
HEATING
USB
POWER
LAN
Input
Reverse Voltage Protection
Current and Voltage tracking
Flash
only 100mA in a KS! And no damage to Ic!. But check for current spikes thouh frequenzy limited to ~1k though
Make sure C10 is close to pin 44 of RP2040
Buck
Reset
Messure
VCC wrong!!! Output Resistors Missing
Crystal
